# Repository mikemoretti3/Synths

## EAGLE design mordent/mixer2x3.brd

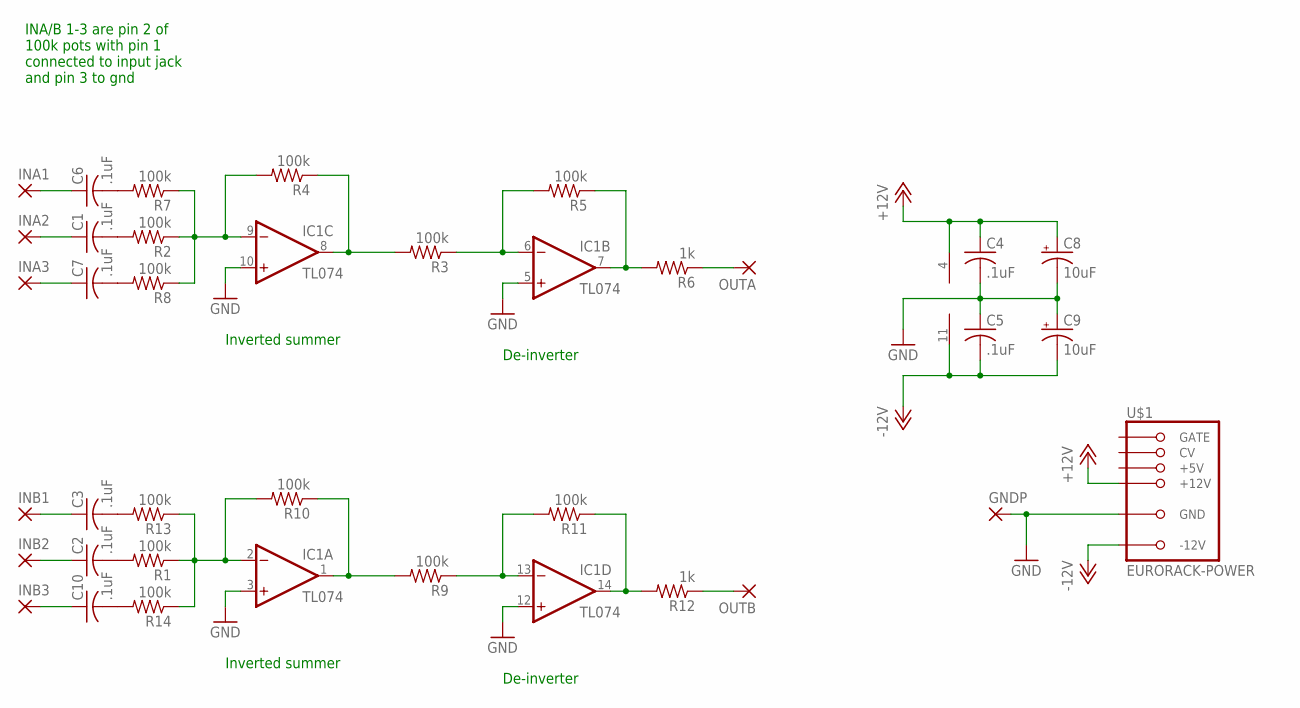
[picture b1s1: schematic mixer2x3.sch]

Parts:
C1, C2, C3, C4, C5, C6, C7, C10: .1uF; C050-025X075
C8, C9: 10uF; E2,5-5
GNDP: 2,54/1,0
IC1: TL074; DIL14
INA1, INA2, INA3: 2,54/1,0
INB1, INB2, INB3: 2,54/1,0
OUTA: 2,54/1,0
OUTB: 2,54/1,0
R1, R2, R3, R4, R5, R7, R8, R9, R10, R11, R13, R14: 100k; 0207/10
R6, R12: 1k; 0207/10
U$1: EURORACK-POWER; PINSHRD_PTH_2X8

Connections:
+12V: C4.1, C8.+, IC1.4 (V+), U$1.+12V@1 (+12V), U$1.+12V@2 (+12V)
-12V: C5.2, C9.-, IC1.11 (V-), U$1.-12V@1 (-12V), U$1.-12V@2 (-12V)
GND: C4.2, C5.1, C8.-, C9.+, GNDP.1, IC1.3 (+IN), IC1.5 (+IN), IC1.10 (+IN), IC1.12 (+IN), U$1.GND@1 (GND), U$1.GND@2 (GND), U$1.GND@3 (GND), U$1.GND@4 (GND), U$1.GND@5 (GND), U$1.GND@6 (GND)
unnamed: IC1.7 (OUT), R5.1, R6.2
unnamed: IC1.9 (-IN), R2.1, R4.2, R7.1, R8.1
unnamed: IC1.8 (OUT), R3.2, R4.1
unnamed: IC1.6 (-IN), R3.1, R5.2
unnamed: C1.2, R2.2
unnamed: OUTA.1, R6.1
unnamed: C6.1, INA1.1
unnamed: C6.2, R7.2
unnamed: C1.1, INA2.1
unnamed: C7.2, R8.2
unnamed: C7.1, INA3.1
unnamed: IC1.14 (OUT), R11.1, R12.2
unnamed: IC1.2 (-IN), R1.1, R10.2, R13.1, R14.1
unnamed: IC1.1 (OUT), R9.2, R10.1
unnamed: IC1.13 (-IN), R9.1, R11.2
unnamed: C2.2, R1.2
unnamed: OUTB.1, R12.1
unnamed: C3.2, R13.2
unnamed: C10.2, R14.2
unnamed: C3.1, INB1.1
unnamed: C2.1, INB2.1
unnamed: C10.1, INB3.1

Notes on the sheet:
INA/B 1-3 are pin 2 of 100k pots with pin 1 connected to input jack and pin 3 to gnd
Inverted summer
De-inverter

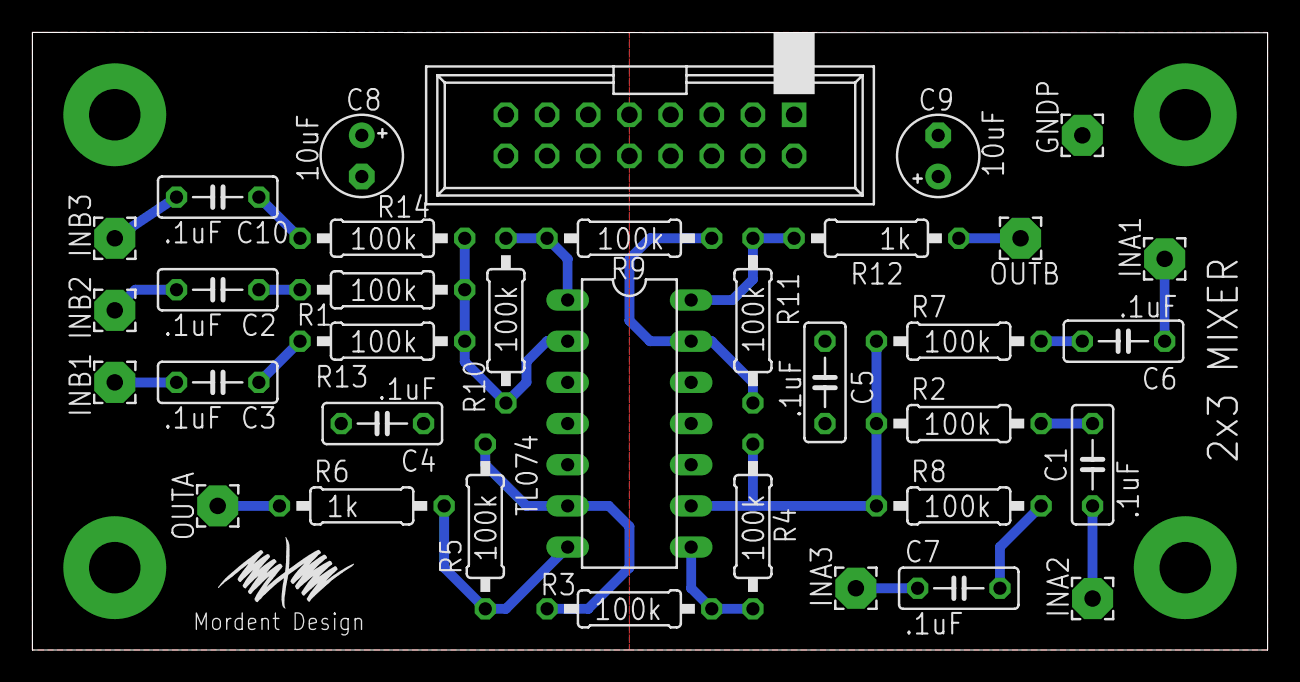
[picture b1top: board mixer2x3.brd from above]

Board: 2 copper layers, 76.2 x 38.1 mm, 35 parts (0 on the bottom side), 25 nets.

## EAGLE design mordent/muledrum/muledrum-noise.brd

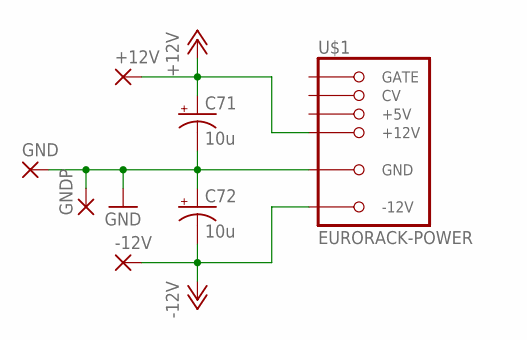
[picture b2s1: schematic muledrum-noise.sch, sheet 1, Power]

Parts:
+12V: 2,54/1,0
-12V: 2,54/1,0
C71, C72: 10u; E2,5-5
GND: 2,54/1,0
GNDP: 2,54/1,0
U$1: EURORACK-POWER; PINSHRD_PTH_2X8

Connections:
+12V: +12V.1, C71.+, U$1.+12V@1 (+12V), U$1.+12V@2 (+12V); also elsewhere on the board
-12V: -12V.1, C72.-, U$1.-12V@1 (-12V), U$1.-12V@2 (-12V); also elsewhere on the board
GND: C71.-, C72.+, GND.1, GNDP.1, U$1.GND@1 (GND), U$1.GND@2 (GND), U$1.GND@3 (GND), U$1.GND@4 (GND), U$1.GND@5 (GND), U$1.GND@6 (GND); also elsewhere on the board

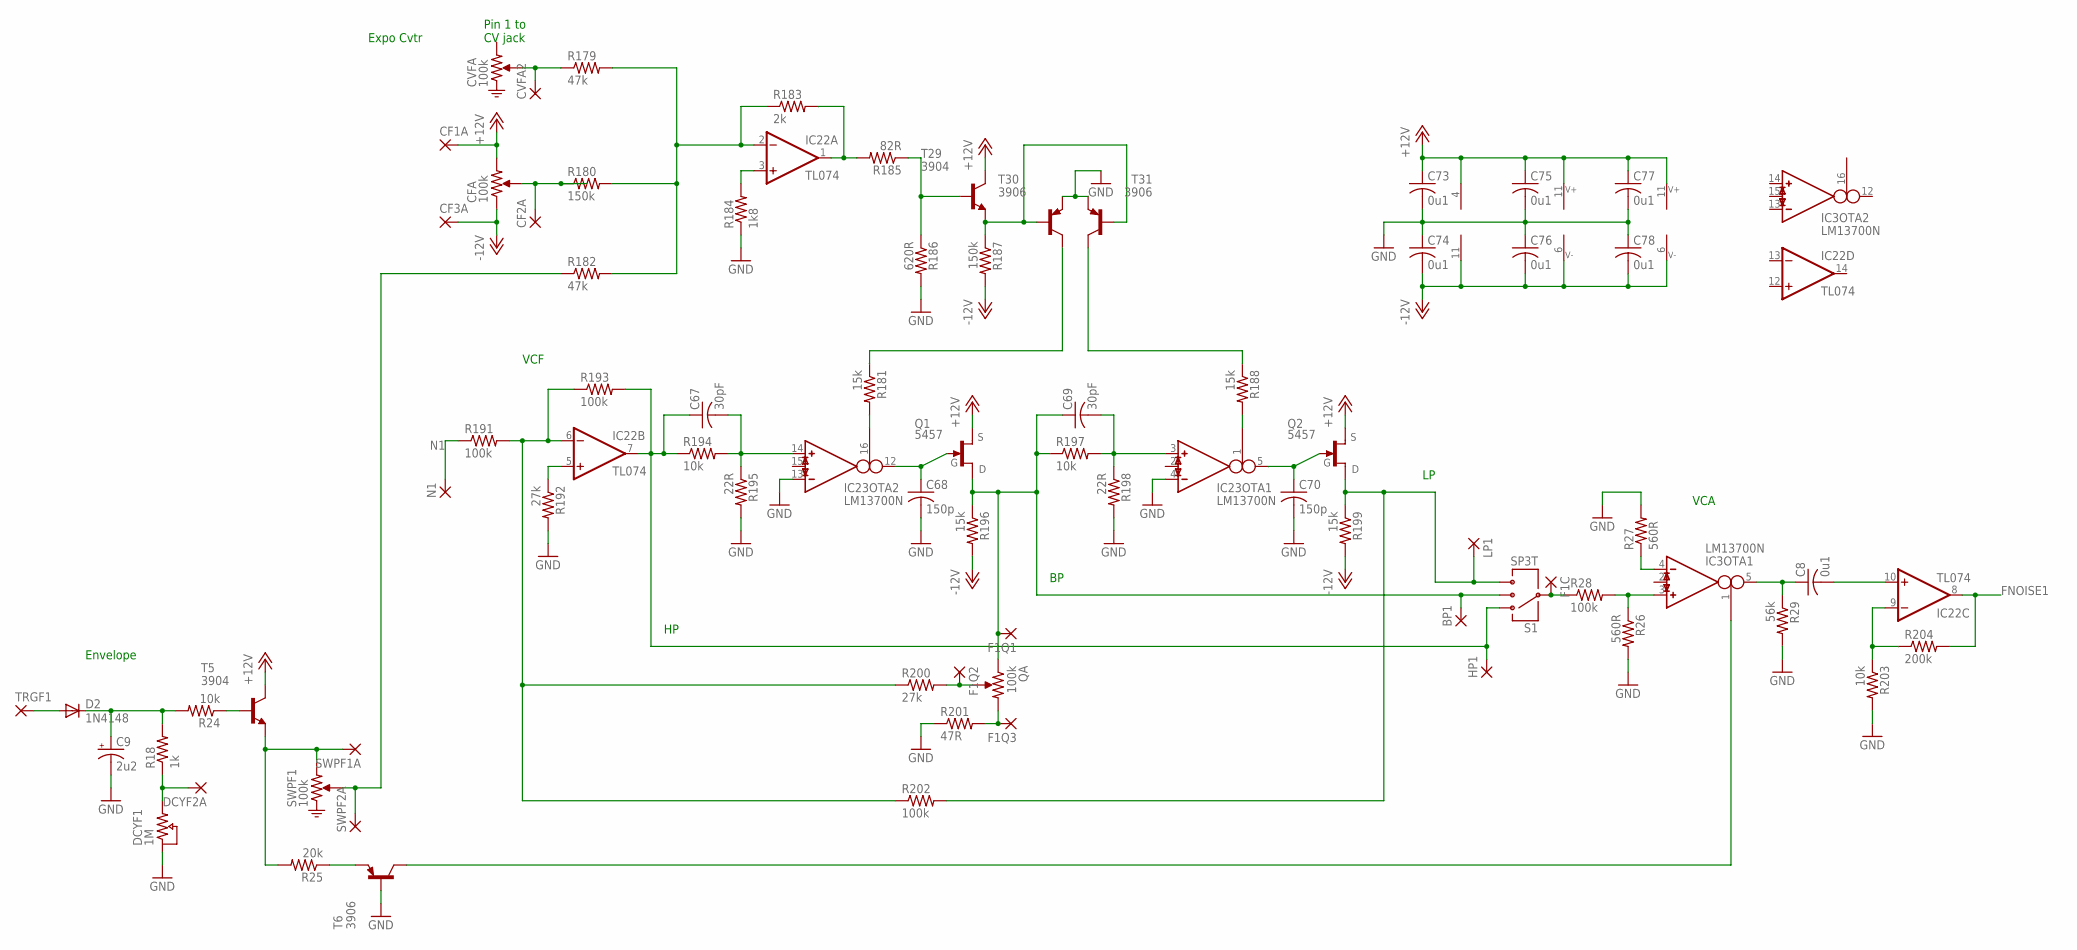
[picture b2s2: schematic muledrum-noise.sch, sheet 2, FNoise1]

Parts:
BP1: 2,54/1,0
C8, C73, C74, C75, C76, C77, C78: 0u1; C050-025X075
C9: 2u2; E2,5-5
C67, C69: 30pF; C050-025X075
C68, C70: 150p; C050-025X075
CF1A, CF2A, CF3A: 2,54/1,0
CVFA2: 2,54/1,0
D2: 1N4148; DO35-7
DCYF2A: 2,54/1,0
F1C, F1Q1, F1Q2, F1Q3: 2,54/1,0
HP1: 2,54/1,0
IC3, IC23: LM13700N; DIL16
IC22: TL074; DIL14
LP1: 2,54/1,0
N1: 2,54/1,0
Q1, Q2: 5457; TO92-EBC
R18: 1k; 0207/10
R24, R194, R197, R203: 10k; 0207/10
R25: 20k; 0207/10
R26, R27: 560R; 0207/10
R28, R191, R193, R202: 100k; 0207/10
R29: 56k; 0207/10
R179, R182: 47k; 0207/10
R180, R187: 150k; 0207/10
R181, R188, R196, R199: 15k; 0207/10
R183: 2k; 0207/10
R184: 1k8; 0207/10
R185: 82R; 0207/10
R186: 620R; 0207/10
R192, R200: 27k; 0207/10
R195, R198: 22R; 0207/10
R201: 47R; 0207/10
R204: 200k; 0207/10
SWPF1A, SWPF2A: 2,54/1,0
T5, T29: 3904; TO92-EBC
T6, T30, T31: 3906; TO92-EBC
TRGF1: 2,54/1,0

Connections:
+12V: C73.1, C75.1, C77.1, CF1A.1, IC3.11 (7), IC22.4 (V+), IC23.11 (7), Q1.E (S), Q2.E (S), T5.C, T29.C; also elsewhere on the board
-12V: C74.2, C76.2, C78.2, CF3A.1, IC3.6 (4), IC22.11 (V-), IC23.6 (4), R187.2, R196.2, R199.2; also elsewhere on the board
FNOISE1: IC22.8 (OUT), R204.2; also elsewhere on the board
GND: C9.-, C68.2, C70.2, C73.2, C74.1, C75.2, C76.1, C77.2, C78.1, IC23.4 (IN_N), IC23.13 (IN_N), R26.2, R27.2, R29.2, R184.1, R186.2, R192.2, R195.2, R198.2, R201.1, R203.2, T6.B, T30.E, T31.E; also elsewhere on the board
N1: N1.1, R191.1
unnamed: C9.+, D2.C, R18.2, R24.2
unnamed: R24.1, T5.B
unnamed: R25.2, SWPF1A.1, T5.E
unnamed: R25.1, T6.E
unnamed: F1C.1, R28.1
unnamed: IC3.3 (IN_P), R26.1, R28.2
unnamed: IC3.4 (IN_N), R27.1
unnamed: C8.1, IC3.5 (OUT), R29.1
unnamed: D2.A, TRGF1.1
unnamed: DCYF2A.1, R18.1
unnamed: R182.1, SWPF2A.1
unnamed: CVFA2.1, R179.1
unnamed: CF2A.1, R180.1
unnamed: IC22.2 (-IN), R179.2, R180.2, R182.2, R183.1
unnamed: C8.2, IC22.10 (+IN)
unnamed: IC22.1 (OUT), R183.2, R185.2
unnamed: IC22.3 (+IN), R184.2
unnamed: R185.1, R186.1, T29.B
unnamed: R187.1, T29.E, T30.B, T31.B
unnamed: R181.1, T30.C
unnamed: R188.1, T31.C
unnamed: IC22.6 (-IN), R191.2, R193.1, R200.1, R202.1
unnamed: IC22.5 (+IN), R192.1
unnamed: IC3.1 (I_BIAS), T6.C
unnamed: C67.2, IC23.14 (IN_P), R194.2, R195.1
unnamed: C68.1, IC23.12 (OUT), Q1.C (G)
unnamed: C70.1, IC23.5 (OUT), Q2.C (G)
unnamed: IC23.16 (I_BIAS), R181.2
unnamed: IC22.9 (-IN), R203.1, R204.1
unnamed: C69.2, IC23.3 (IN_P), R197.2, R198.1
unnamed: IC23.1 (I_BIAS), R188.2
unnamed: F1Q2.1, R200.2
unnamed: F1Q3.1, R201.2
unnamed: C67.1, HP1.1, IC22.7 (OUT), R193.2, R194.1
unnamed: BP1.1, C69.1, F1Q1.1, Q1.B (D), R196.1, R197.1
unnamed: LP1.1, Q2.B (D), R199.1, R202.2

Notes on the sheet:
Envelope
VCA
VCF
Expo Cvtr
Pin 1 to CV jack

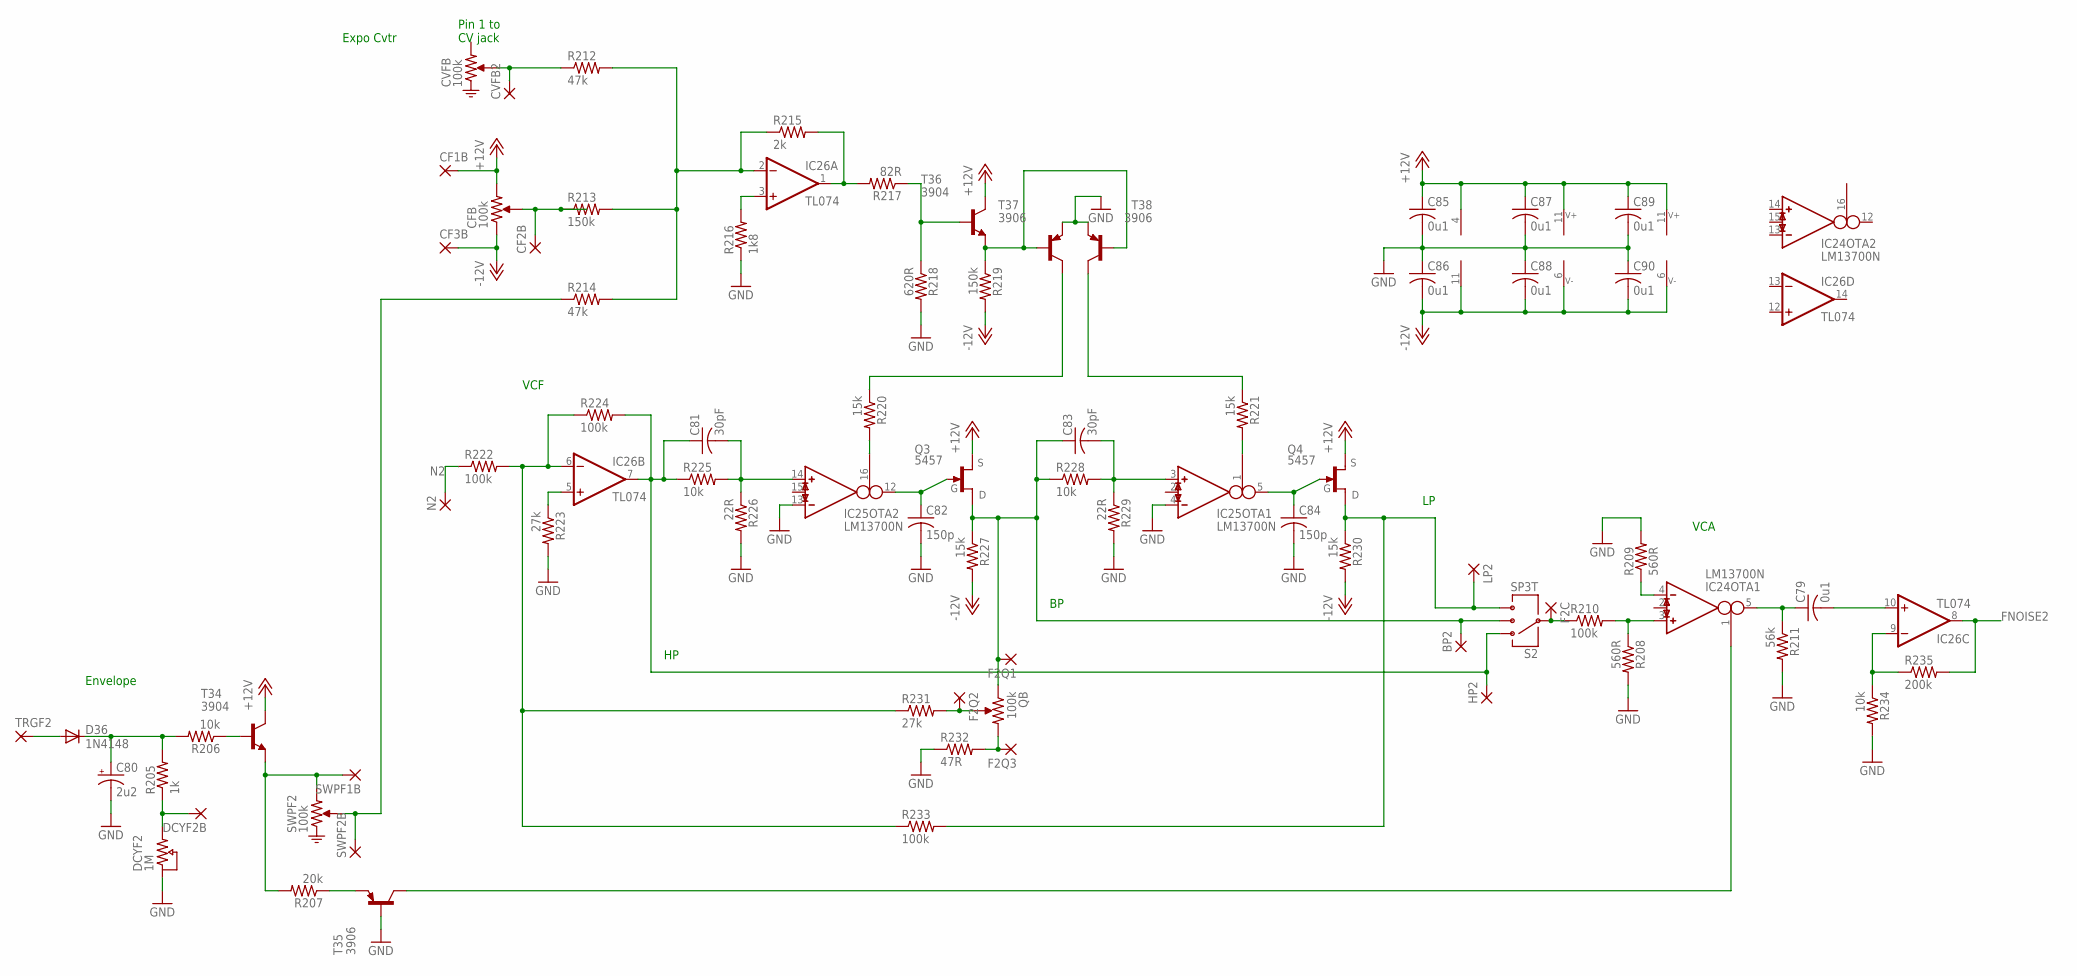
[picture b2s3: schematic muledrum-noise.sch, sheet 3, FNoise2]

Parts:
BP2: 2,54/1,0
C79, C85, C86, C87, C88, C89, C90: 0u1; C050-025X075
C80: 2u2; E2,5-5
C81, C83: 30pF; C050-025X075
C82, C84: 150p; C050-025X075
CF1B, CF2B, CF3B: 2,54/1,0
CVFB2: 2,54/1,0
D36: 1N4148; DO35-7
DCYF2B: 2,54/1,0
F2C, F2Q1, F2Q2, F2Q3: 2,54/1,0
HP2: 2,54/1,0
IC24, IC25: LM13700N; DIL16
IC26: TL074; DIL14
LP2: 2,54/1,0
N2: 2,54/1,0
Q3, Q4: 5457; TO92-EBC
R205: 1k; 0207/10
R206, R225, R228, R234: 10k; 0207/10
R207: 20k; 0207/10
R208, R209: 560R; 0207/10
R210, R222, R224, R233: 100k; 0207/10
R211: 56k; 0207/10
R212, R214: 47k; 0207/10
R213, R219: 150k; 0207/10
R215: 2k; 0207/10
R216: 1k8; 0207/10
R217: 82R; 0207/10
R218: 620R; 0207/10
R220, R221, R227, R230: 15k; 0207/10
R223, R231: 27k; 0207/10
R226, R229: 22R; 0207/10
R232: 47R; 0207/10
R235: 200k; 0207/10
SWPF1B, SWPF2B: 2,54/1,0
T34, T36: 3904; TO92-EBC
T35, T37, T38: 3906; TO92-EBC
TRGF2: 2,54/1,0

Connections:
+12V: C85.1, C87.1, C89.1, CF1B.1, IC24.11 (7), IC25.11 (7), IC26.4 (V+), Q3.E (S), Q4.E (S), T34.C, T36.C; also elsewhere on the board
-12V: C86.2, C88.2, C90.2, CF3B.1, IC24.6 (4), IC25.6 (4), IC26.11 (V-), R219.2, R227.2, R230.2; also elsewhere on the board
FNOISE2: IC26.8 (OUT), R235.2; also elsewhere on the board
GND: C80.-, C82.2, C84.2, C85.2, C86.1, C87.2, C88.1, C89.2, C90.1, IC25.4 (IN_N), IC25.13 (IN_N), R208.2, R209.2, R211.2, R216.1, R218.2, R223.2, R226.2, R229.2, R232.1, R234.2, T35.B, T37.E, T38.E; also elsewhere on the board
N2: N2.1, R222.1
unnamed: CVFB2.1, R212.1
unnamed: C80.+, D36.C, R205.2, R206.2
unnamed: R206.1, T34.B
unnamed: R207.2, SWPF1B.1, T34.E
unnamed: R207.1, T35.E
unnamed: IC24.3 (IN_P), R208.1, R210.2
unnamed: IC24.4 (IN_N), R209.1
unnamed: C79.1, IC24.5 (OUT), R211.1
unnamed: D36.A, TRGF2.1
unnamed: DCYF2B.1, R205.1
unnamed: R214.1, SWPF2B.1
unnamed: IC26.2 (-IN), R212.2, R213.2, R214.2, R215.1
unnamed: IC26.1 (OUT), R215.2, R217.2
unnamed: IC26.3 (+IN), R216.2
unnamed: R217.1, R218.1, T36.B
unnamed: R219.1, T36.E, T37.B, T38.B
unnamed: R220.1, T37.C
unnamed: R221.1, T38.C
unnamed: CF2B.1, R213.1
unnamed: IC26.6 (-IN), R222.2, R224.1, R231.1, R233.1
unnamed: IC26.5 (+IN), R223.1
unnamed: C81.2, IC25.14 (IN_P), R225.2, R226.1
unnamed: C82.1, IC25.12 (OUT), Q3.C (G)
unnamed: IC25.16 (I_BIAS), R220.2
unnamed: C83.2, IC25.3 (IN_P), R228.2, R229.1
unnamed: C84.1, IC25.5 (OUT), Q4.C (G)
unnamed: IC25.1 (I_BIAS), R221.2
unnamed: F2Q2.1, R231.2
unnamed: F2Q3.1, R232.2
unnamed: C81.1, HP2.1, IC26.7 (OUT), R224.2, R225.1
unnamed: BP2.1, C83.1, F2Q1.1, Q3.B (D), R227.1, R228.1
unnamed: LP2.1, Q4.B (D), R230.1, R233.2
unnamed: F2C.1, R210.1
unnamed: IC24.1 (I_BIAS), T35.C
unnamed: C79.2, IC26.10 (+IN)
unnamed: IC26.9 (-IN), R234.1, R235.1

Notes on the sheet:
Envelope
VCA
VCF
Expo Cvtr
Pin 1 to CV jack

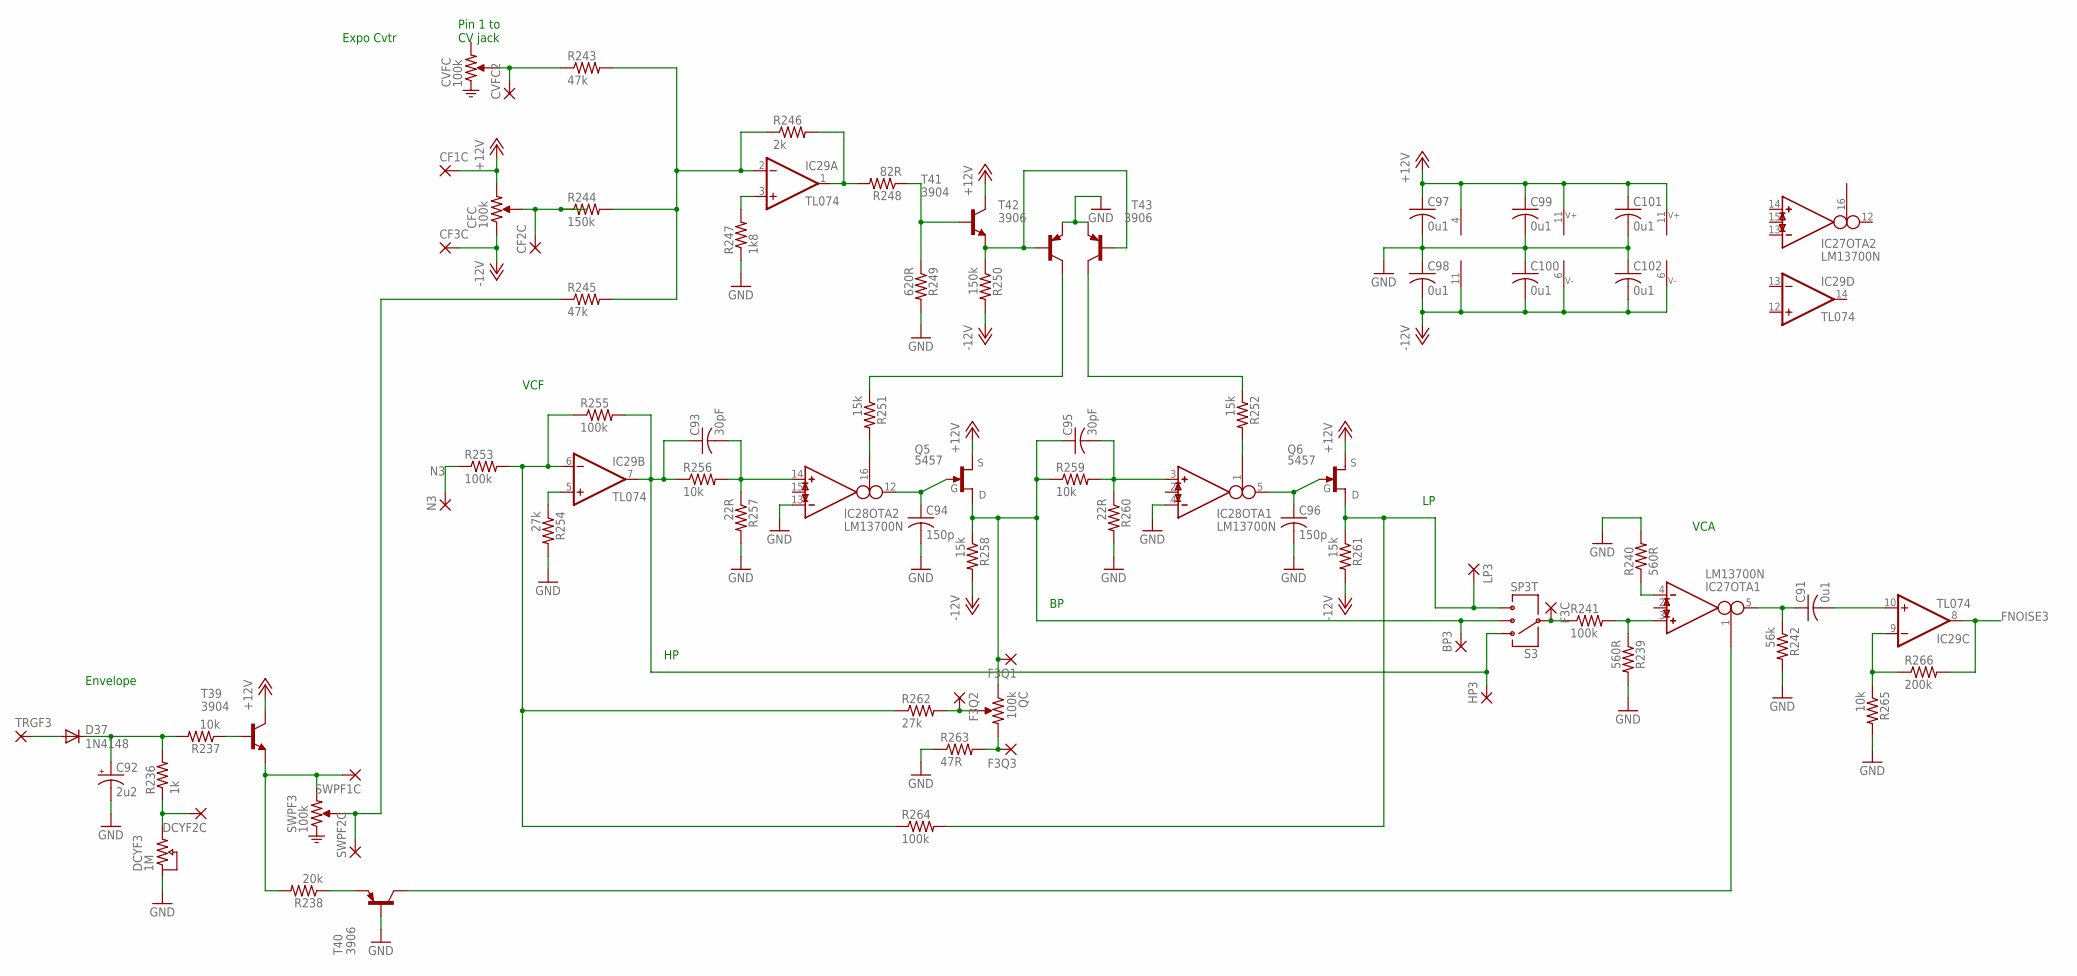
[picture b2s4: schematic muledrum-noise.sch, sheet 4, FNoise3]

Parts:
BP3: 2,54/1,0
C91, C97, C98, C99, C100, C101, C102: 0u1; C050-025X075
C92: 2u2; E2,5-5
C93, C95: 30pF; C050-025X075
C94, C96: 150p; C050-025X075
CF1C, CF2C, CF3C: 2,54/1,0
CVFC2: 2,54/1,0
D37: 1N4148; DO35-7
DCYF2C: 2,54/1,0
F3C: 2,54/1,0
F3Q1, F3Q2, F3Q3: 2,54/1,1
HP3: 2,54/1,0
IC27, IC28: LM13700N; DIL16
IC29: TL074; DIL14
LP3: 2,54/1,0
N3: 2,54/1,0
Q5, Q6: 5457; TO92-EBC
R236: 1k; 0207/10
R237, R256, R259, R265: 10k; 0207/10
R238: 20k; 0207/10
R239, R240: 560R; 0207/10
R241, R253, R255, R264: 100k; 0207/10
R242: 56k; 0207/10
R243, R245: 47k; 0207/10
R244, R250: 150k; 0207/10
R246: 2k; 0207/10
R247: 1k8; 0207/10
R248: 82R; 0207/10
R249: 620R; 0207/10
R251, R252, R258, R261: 15k; 0207/10
R254, R262: 27k; 0207/10
R257, R260: 22R; 0207/10
R263: 47R; 0207/10
R266: 200k; 0207/10
SWPF1C, SWPF2C: 2,54/1,0
T39, T41: 3904; TO92-EBC
T40, T42, T43: 3906; TO92-EBC
TRGF3: 2,54/1,0

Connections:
+12V: C97.1, C99.1, C101.1, CF1C.1, IC27.11 (7), IC28.11 (7), IC29.4 (V+), Q5.E (S), Q6.E (S), T39.C, T41.C; also elsewhere on the board
-12V: C98.2, C100.2, C102.2, CF3C.1, IC27.6 (4), IC28.6 (4), IC29.11 (V-), R250.2, R258.2, R261.2; also elsewhere on the board
FNOISE3: IC29.8 (OUT), R266.2; also elsewhere on the board
GND: C92.-, C94.2, C96.2, C97.2, C98.1, C99.2, C100.1, C101.2, C102.1, IC28.4 (IN_N), IC28.13 (IN_N), R239.2, R240.2, R242.2, R247.1, R249.2, R254.2, R257.2, R260.2, R263.1, R265.2, T40.B, T42.E, T43.E; also elsewhere on the board
N3: N3.1, R253.1
unnamed: CVFC2.1, R243.1
unnamed: C92.+, D37.C, R236.2, R237.2
unnamed: R237.1, T39.B
unnamed: R238.2, SWPF1C.1, T39.E
unnamed: R238.1, T40.E
unnamed: IC27.3 (IN_P), R239.1, R241.2
unnamed: IC27.4 (IN_N), R240.1
unnamed: C91.1, IC27.5 (OUT), R242.1
unnamed: D37.A, TRGF3.1
unnamed: DCYF2C.1, R236.1
unnamed: R245.1, SWPF2C.1
unnamed: IC29.2 (-IN), R243.2, R244.2, R245.2, R246.1
unnamed: IC29.1 (OUT), R246.2, R248.2
unnamed: IC29.3 (+IN), R247.2
unnamed: R248.1, R249.1, T41.B
unnamed: R250.1, T41.E, T42.B, T43.B
unnamed: R251.1, T42.C
unnamed: R252.1, T43.C
unnamed: CF2C.1, R244.1
unnamed: IC29.6 (-IN), R253.2, R255.1, R262.1, R264.1
unnamed: IC29.5 (+IN), R254.1
unnamed: C93.2, IC28.14 (IN_P), R256.2, R257.1
unnamed: C94.1, IC28.12 (OUT), Q5.C (G)
unnamed: IC28.16 (I_BIAS), R251.2
unnamed: C95.2, IC28.3 (IN_P), R259.2, R260.1
unnamed: C96.1, IC28.5 (OUT), Q6.C (G)
unnamed: IC28.1 (I_BIAS), R252.2
unnamed: F3Q2.1, R262.2
unnamed: F3Q3.1, R263.2
unnamed: C93.1, HP3.1, IC29.7 (OUT), R255.2, R256.1
unnamed: BP3.1, C95.1, F3Q1.1, Q5.B (D), R258.1, R259.1
unnamed: LP3.1, Q6.B (D), R261.1, R264.2
unnamed: F3C.1, R241.1
unnamed: IC27.1 (I_BIAS), T40.C
unnamed: C91.2, IC29.10 (+IN)
unnamed: IC29.9 (-IN), R265.1, R266.1

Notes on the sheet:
Envelope
VCA
VCF
Expo Cvtr
Pin 1 to CV jack

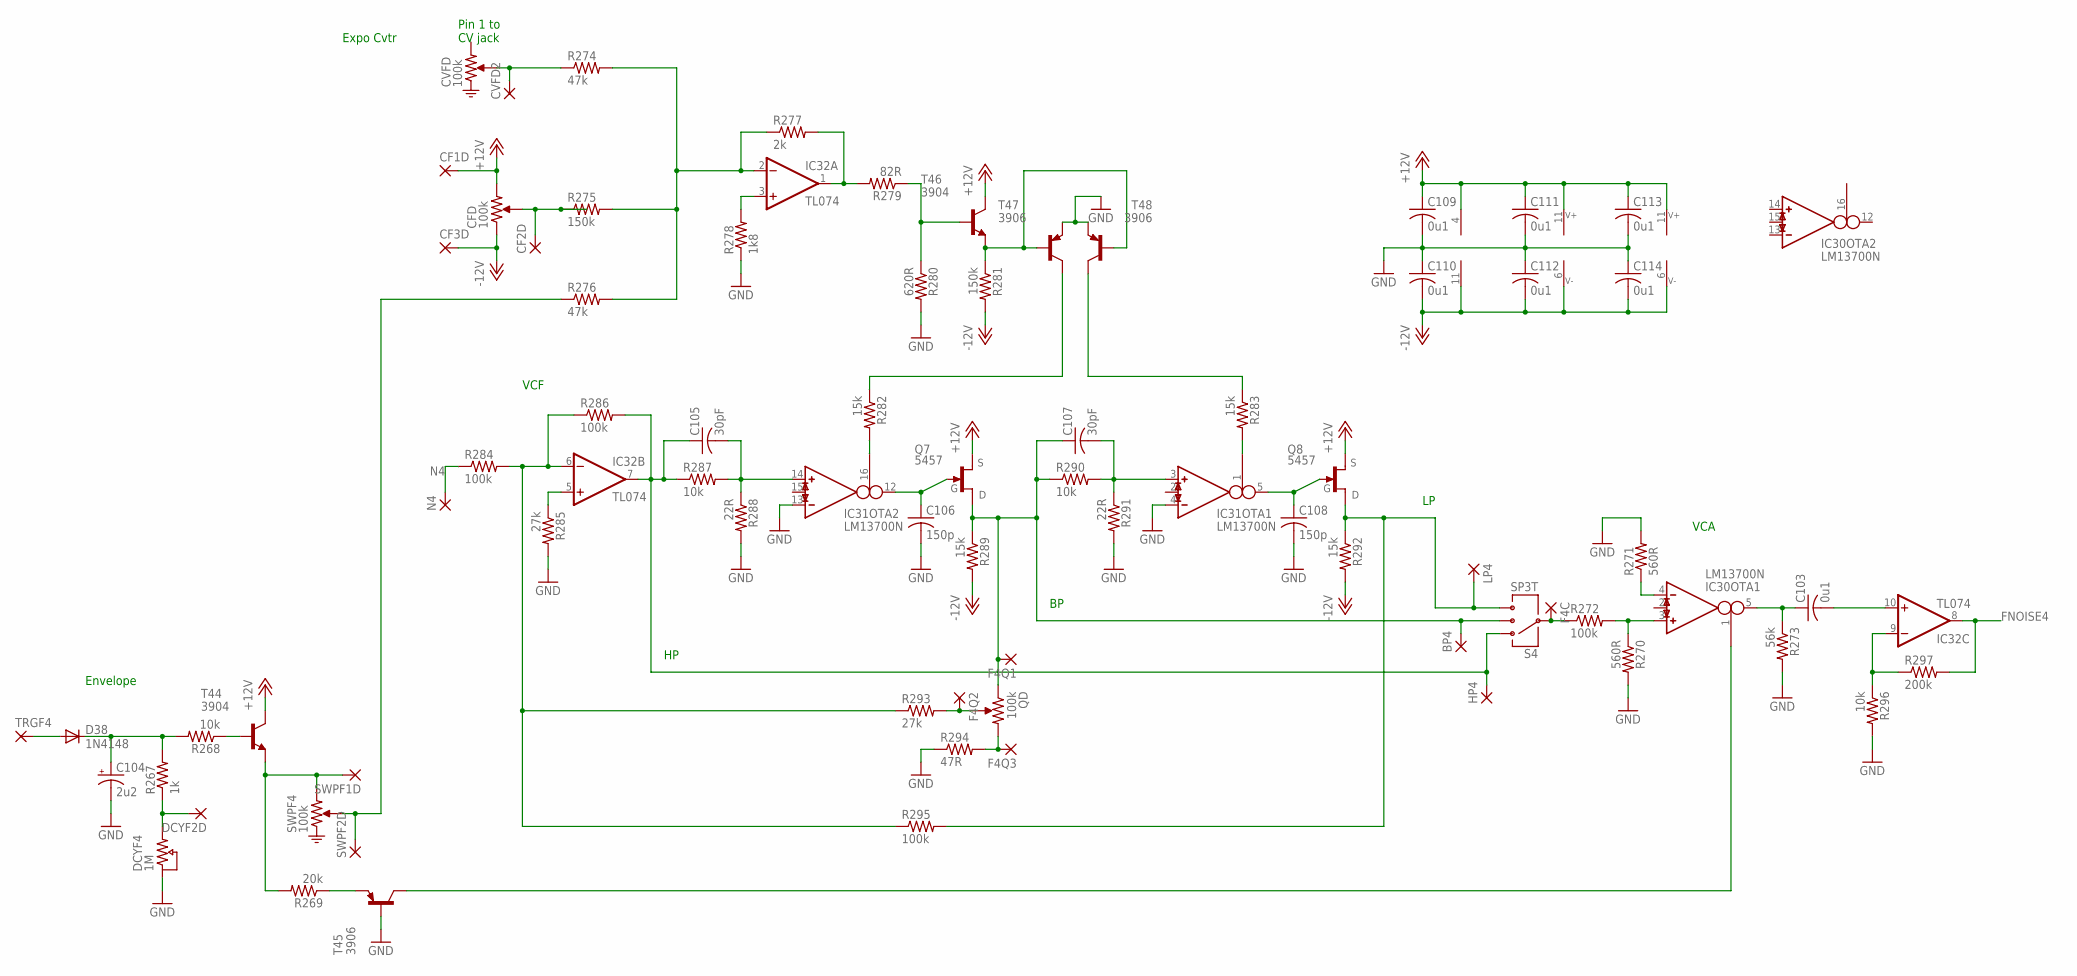
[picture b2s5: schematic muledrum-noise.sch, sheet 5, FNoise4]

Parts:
BP4: 2,54/1,0
C103, C109, C110, C111, C112, C113, C114: 0u1; C050-025X075
C104: 2u2; E2,5-5
C105, C107: 30pF; C050-025X075
C106, C108: 150p; C050-025X075
CF1D, CF2D, CF3D: 2,54/1,0
CVFD2: 2,54/1,0
D38: 1N4148; DO35-7
DCYF2D: 2,54/1,0
F4C, F4Q1, F4Q2, F4Q3: 2,54/1,0
HP4: 2,54/1,0
IC30, IC31: LM13700N; DIL16
IC32: TL074; DIL14
LP4: 2,54/1,0
N4: 2,54/1,0
Q7, Q8: 5457; TO92-EBC
R267: 1k; 0207/10
R268, R287, R290, R296: 10k; 0207/10
R269: 20k; 0207/10
R270, R271: 560R; 0207/10
R272, R284, R286, R295: 100k; 0207/10
R273: 56k; 0207/10
R274, R276: 47k; 0207/10
R275, R281: 150k; 0207/10
R277: 2k; 0207/10
R278: 1k8; 0207/10
R279: 82R; 0207/10
R280: 620R; 0207/10
R282, R283, R289, R292: 15k; 0207/10
R285, R293: 27k; 0207/10
R288, R291: 22R; 0207/10
R294: 47R; 0207/10
R297: 200k; 0207/10
SWPF1D, SWPF2D: 2,54/1,0
T44, T46: 3904; TO92-EBC
T45, T47, T48: 3906; TO92-EBC
TRGF4: 2,54/1,0

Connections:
+12V: C109.1, C111.1, C113.1, CF1D.1, IC30.11 (7), IC31.11 (7), IC32.4 (V+), Q7.E (S), Q8.E (S), T44.C, T46.C; also elsewhere on the board
-12V: C110.2, C112.2, C114.2, CF3D.1, IC30.6 (4), IC31.6 (4), IC32.11 (V-), R281.2, R289.2, R292.2; also elsewhere on the board
FNOISE4: IC32.8 (OUT), R297.2; also elsewhere on the board
GND: C104.-, C106.2, C108.2, C109.2, C110.1, C111.2, C112.1, C113.2, C114.1, IC31.4 (IN_N), IC31.13 (IN_N), R270.2, R271.2, R273.2, R278.1, R280.2, R285.2, R288.2, R291.2, R294.1, R296.2, T45.B, T47.E, T48.E; also elsewhere on the board
N4: N4.1, R284.1
unnamed: CVFD2.1, R274.1
unnamed: C104.+, D38.C, R267.2, R268.2
unnamed: R268.1, T44.B
unnamed: R269.2, SWPF1D.1, T44.E
unnamed: R269.1, T45.E
unnamed: IC30.3 (IN_P), R270.1, R272.2
unnamed: IC30.4 (IN_N), R271.1
unnamed: C103.1, IC30.5 (OUT), R273.1
unnamed: D38.A, TRGF4.1
unnamed: DCYF2D.1, R267.1
unnamed: R276.1, SWPF2D.1
unnamed: IC32.2 (-IN), R274.2, R275.2, R276.2, R277.1
unnamed: IC32.1 (OUT), R277.2, R279.2
unnamed: IC32.3 (+IN), R278.2
unnamed: R279.1, R280.1, T46.B
unnamed: R281.1, T46.E, T47.B, T48.B
unnamed: R282.1, T47.C
unnamed: R283.1, T48.C
unnamed: CF2D.1, R275.1
unnamed: IC32.6 (-IN), R284.2, R286.1, R293.1, R295.1
unnamed: IC32.5 (+IN), R285.1
unnamed: C105.2, IC31.14 (IN_P), R287.2, R288.1
unnamed: C106.1, IC31.12 (OUT), Q7.C (G)
unnamed: IC31.16 (I_BIAS), R282.2
unnamed: C107.2, IC31.3 (IN_P), R290.2, R291.1
unnamed: C108.1, IC31.5 (OUT), Q8.C (G)
unnamed: IC31.1 (I_BIAS), R283.2
unnamed: F4Q2.1, R293.2
unnamed: F4Q3.1, R294.2
unnamed: C105.1, HP4.1, IC32.7 (OUT), R286.2, R287.1
unnamed: BP4.1, C107.1, F4Q1.1, Q7.B (D), R289.1, R290.1
unnamed: LP4.1, Q8.B (D), R292.1, R295.2
unnamed: F4C.1, R272.1
unnamed: IC30.1 (I_BIAS), T45.C
unnamed: C103.2, IC32.10 (+IN)
unnamed: IC32.9 (-IN), R296.1, R297.1

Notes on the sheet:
Envelope
VCA
VCF
Expo Cvtr
Pin 1 to CV jack

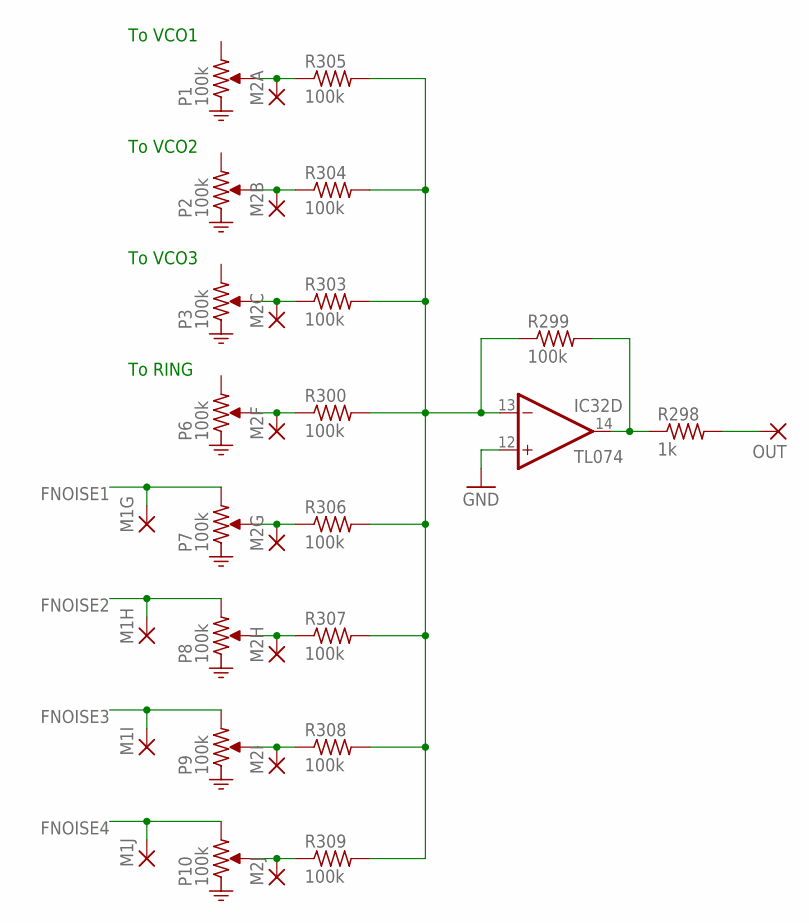
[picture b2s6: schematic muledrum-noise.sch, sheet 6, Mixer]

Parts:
IC32: TL074; DIL14
M1G, M1H, M1I, M1J, M2A, M2B, M2C, M2F, M2G, M2H, M2I, M2J: 2,54/1,0
OUT: 2,54/1,0
R298: 1k; 0207/10
R299, R300, R303, R304, R305, R306, R307, R308, R309: 100k; 0207/10

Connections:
FNOISE1: M1G.1; also elsewhere on the board
FNOISE2: M1H.1; also elsewhere on the board
FNOISE3: M1I.1; also elsewhere on the board
FNOISE4: M1J.1; also elsewhere on the board
GND: IC32.12 (+IN); also elsewhere on the board
unnamed: IC32.13 (-IN), R299.1, R300.2, R303.2, R304.2, R305.2, R306.2, R307.2, R308.2, R309.2
unnamed: IC32.14 (OUT), R298.1, R299.2
unnamed: OUT.1, R298.2
unnamed: M2A.1, R305.1
unnamed: M2B.1, R304.1
unnamed: M2C.1, R303.1
unnamed: M2F.1, R300.1
unnamed: M2G.1, R306.1
unnamed: M2H.1, R307.1
unnamed: M2I.1, R308.1
unnamed: M2J.1, R309.1

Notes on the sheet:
To VCO1
To VCO2
To VCO3
To RING

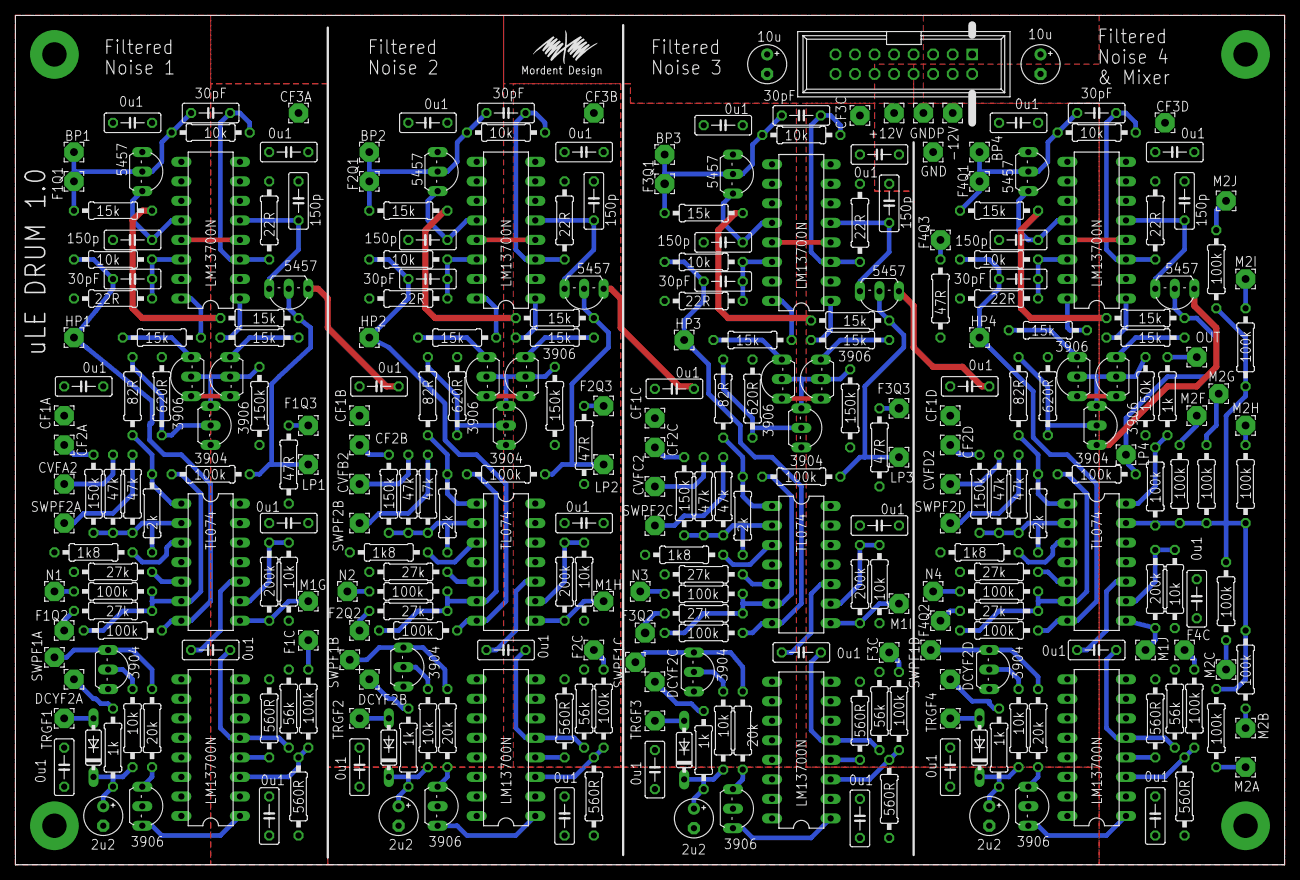
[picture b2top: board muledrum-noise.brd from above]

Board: 2 copper layers, 165.1 x 110.5 mm, 310 parts (0 on the bottom side), 166 nets.
